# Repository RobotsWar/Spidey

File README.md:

# This project has moved

## Spidey is now Metabot
## [https://github.com/Rhoban/Metabot/](https://github.com/Rhoban/Metabot/)

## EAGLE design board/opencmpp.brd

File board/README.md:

# OpenCM++

[Documentation »](../docs/opencmpp.md)

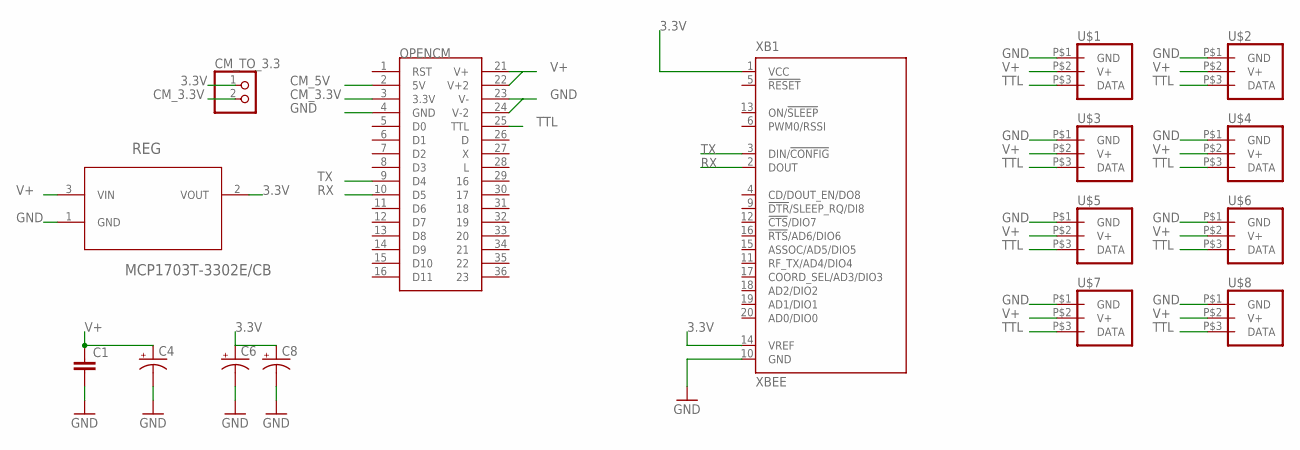
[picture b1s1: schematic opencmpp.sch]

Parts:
C1: C-EU075-032X103; C075-032X103
C4, C6, C8: CAP_POLPTH2; CPOL-RADIAL-10UF-25V
CM_TO_3.3: CONNEC_1X02
OPENCM: OPENCM_REDUC
REG: MCP1703T-3302E/CB; SOT95P300X145-3N
U$1, U$2, U$3, U$4, U$5, U$6, U$7, U$8: XL_320_CONNEC; DXL_320_CONNEC
XB1: XBEE

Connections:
3.3V: C6.1 (+), C8.1 (+), CM_TO_3.3.1, REG.2 (VOUT), XB1.1 (VCC), XB1.14 (VREF)
CM_3.3V: CM_TO_3.3.2, OPENCM.3 (3.3V)
CM_5V: OPENCM.2 (5V)
GND: C1.2, C4.2 (-), C6.2 (-), C8.2 (-), OPENCM.4 (GND), OPENCM.23 (V-), OPENCM.24 (V-2), REG.1 (GND), U$1.P$1 (GND), U$2.P$1 (GND), U$3.P$1 (GND), U$4.P$1 (GND), U$5.P$1 (GND), U$6.P$1 (GND), U$7.P$1 (GND), U$8.P$1 (GND), XB1.10 (GND)
RX: OPENCM.10 (D5), XB1.2 (DOUT)
TTL: OPENCM.25 (TTL), U$1.P$3 (DATA), U$2.P$3 (DATA), U$3.P$3 (DATA), U$4.P$3 (DATA), U$5.P$3 (DATA), U$6.P$3 (DATA), U$7.P$3 (DATA), U$8.P$3 (DATA)
TX: OPENCM.9 (D4), XB1.3 (DIN/!CONFIG)
V+: C1.1, C4.1 (+), OPENCM.21 (V+), OPENCM.22 (V+2), REG.3 (VIN), U$1.P$2 (V+), U$2.P$2 (V+), U$3.P$2 (V+), U$4.P$2 (V+), U$5.P$2 (V+), U$6.P$2 (V+), U$7.P$2 (V+), U$8.P$2 (V+)

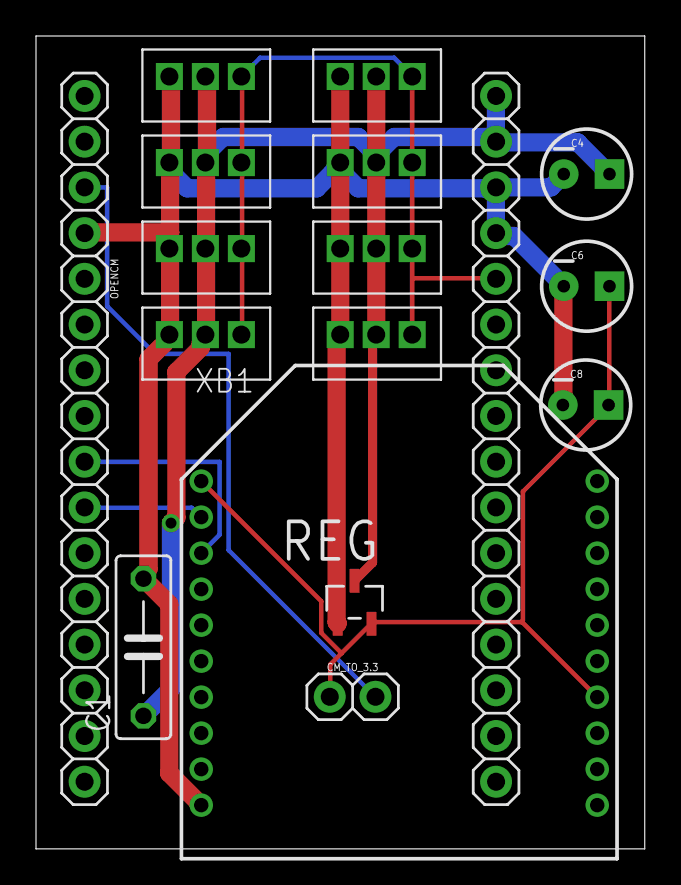
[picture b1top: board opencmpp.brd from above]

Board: 2 copper layers, 33.8 x 45.2 mm, 16 parts (0 on the bottom side), 7 nets.

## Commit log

2014-04-09 Video
2014-04-09 Adding 3D parts and buy list
2014-04-09 OpenCM++
2014-04-10 Adding pulleys
2014-04-10 Adding M2
2014-04-16 Adding png & stl
2014-04-16 GitIgnore
2014-04-16 Updating global stl
2014-04-16 3D source files
2014-04-16 Adding schematics
2014-04-16 Adding parts images
2014-04-16 Typo
2014-04-16 Docs
2014-04-16 Renaming
2014-04-16 Numbering
2014-04-16 Fixing leg directions
2014-04-16 Assemble (wip)
2014-04-16 Assemble
2014-04-16 Assemble & ids (wip)
2014-04-16 Warning
2014-04-16 Bec solder
2014-04-16 Downscaling images
2014-04-16 Images
2014-04-16 Fixing name
2014-04-16 Fixing image
2014-04-16 Bootloader
2014-04-16 Adding return links
2014-04-22 Moving to bootloader sketch
2014-04-22 Adding license
2014-04-22 README
2014-04-22 Adding mistake doc
2014-04-22 OpenCM++ gerber
2014-04-22 OpenCM++ doc
2014-04-22 Fixing images in opencmpp.md
2014-04-22 Updating robot with OpenCM++
2014-04-22 Reducing image
2014-04-22 README fix
2014-04-22 Adding firmware source
2014-04-22 Adding readme
2014-04-22 Adding firmware doc
2014-04-22 Adding windows installation scripts
2014-04-22 Adding information
2014-04-22 Improving prepare script
2014-04-23 Disabling servos commands
2014-04-23 Changing spidey.bin, removing servos commands
2014-04-23 Moving wifly to RC
2014-04-23 Fixing backward mode
2014-04-23 Updating firmware
2014-04-23 Adding support for robotis bootloader
2014-04-23 Moving to robotis-loader.py
2014-04-23 Removing the bootloader hack
2014-04-23 Updating doc
2014-04-23 Updating redirections
2014-04-24 Updating loader
2014-04-28 OpenSCAD versions
2014-04-28 Removing useless line in common.scad
2014-04-28 [OpenSCAD] Adding full assembly
2014-04-28 Tweaking directory structure
2014-04-28 Tweaking & cleaning
2014-04-28 Fixes & cleaning
2014-04-28 Adding make movie
2014-04-28 Restoring transparency
2014-04-28 Increasing bitrate
2014-04-29 Tweak
2014-04-30 Parametric number of legs
2014-04-30 Fixing default value of spidey
2014-04-30 Adding MotorsPerLeg
2014-04-30 Cleaning
2014-04-30 Doc firmware
2014-04-30 Fixes
2014-05-02 Tweaking scad structure
2014-05-02 Adding print-scad
2014-05-02 Fixing body
2014-05-02 Using print flag
2014-05-02 Fixes & improvements
2014-05-02 Factorizing the joins
2014-05-02 Joins
2014-05-02 Joins->Joints
2014-05-02 Fixing for loop
2014-05-02 Displaying BOM only when not printing
2014-05-02 Adding projections
2014-05-05 Fixing size
2014-05-12 3D Refactoring
2014-05-12 Documentation for 3D hacking
2014-05-12 Adding openscad screenshot
2014-05-12 Changing main image
2014-05-12 Removing global stl
2014-05-12 Adding withSize parameter to u part
2014-05-12 Adding scad util thickLine
2014-05-13 Fixing fixation
2014-05-13 Adding gecky robot scad
2014-05-14 Adding ollo screw to u part
2014-05-14 Updating gecky
2014-05-14 Gecky scad refactorization
2014-05-14 Gecky scad print
2014-05-14 Gecky scad in parts for export
2014-05-15 Removing useless difference()
2014-05-18 Fixing crab mode in back
2014-05-20 Gecky scad update
2014-05-21 Adding XL-320 URL
2014-05-26 Fixing side design
2014-05-28 Adding cotation
2014-05-30 Adding make plates (using plater)
2014-05-30 Removing plates before making them
2014-06-09 Commenting kinematic.h (see #3)
2014-06-09 Improving ascii comment (see #3)
2014-06-09 Commenting kinematic.cpp (see #3)
2014-06-17 [README] Updating demo video
2014-07-01 xp shouldn't include l1 in the kinematics formulas
    I have analyzed the formulas, and it seems to me, that the degree which you are subtracting when calculating beta is actually wrong -- you are taking the larger triangle, which begins at a, but you s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
2014-07-02 Adding kinematic in the doc (see #3 and #4)
2014-07-02 Hacking kinematic doc
2014-09-10 Adding (commented) DXL_VERSION_1
2014-09-10 Adding troubleshooting for missing servo
2014-10-01 Motion
2014-10-01 Updating robot links
2014-10-07 LICENSE
2014-10-07 Adding DFPad code
2014-10-08 Adding orientation
2014-10-14 Fixing
2014-10-15 Adding unsafe/safe mode
2014-10-20 U size
2014-10-29 Using .h
2014-11-01 Adding delay to start for motor to boot
2014-11-03 Adding gait selection (WALK & TROT)
2014-12-02 Renaming width to thickness
2014-12-02 Adding screws utils
2014-12-02 Adding child possibility to body
2014-12-02 Adding black arm/grey counterarm
2014-12-02 Fixing double_u orientation
2014-12-02 Adding body screws
2014-12-02 Adding parameters for body screws
2014-12-02 Adding screws square
2014-12-02 Adding batfix
2014-12-02 Adding body batfix (+makefile)
2014-12-05 New parts [WIP]
2014-12-05 New parts list
2014-12-13 Moving to Metabot

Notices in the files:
parts and their libraries:
SparkFun-Capacitors: Licensing: CC v3.0 Share-Alike You are welcome to use this library for commercial purposes.
